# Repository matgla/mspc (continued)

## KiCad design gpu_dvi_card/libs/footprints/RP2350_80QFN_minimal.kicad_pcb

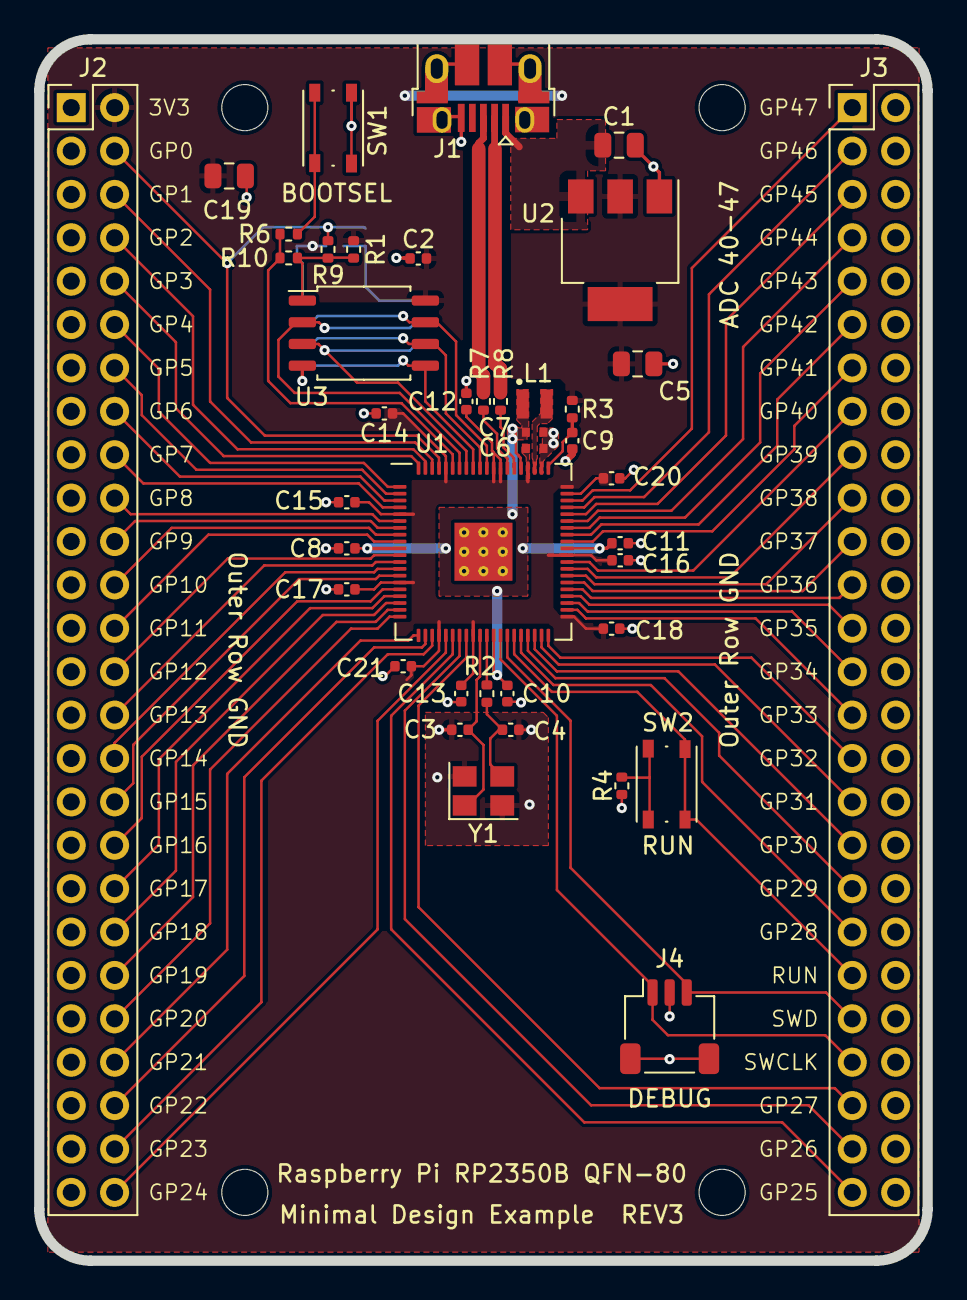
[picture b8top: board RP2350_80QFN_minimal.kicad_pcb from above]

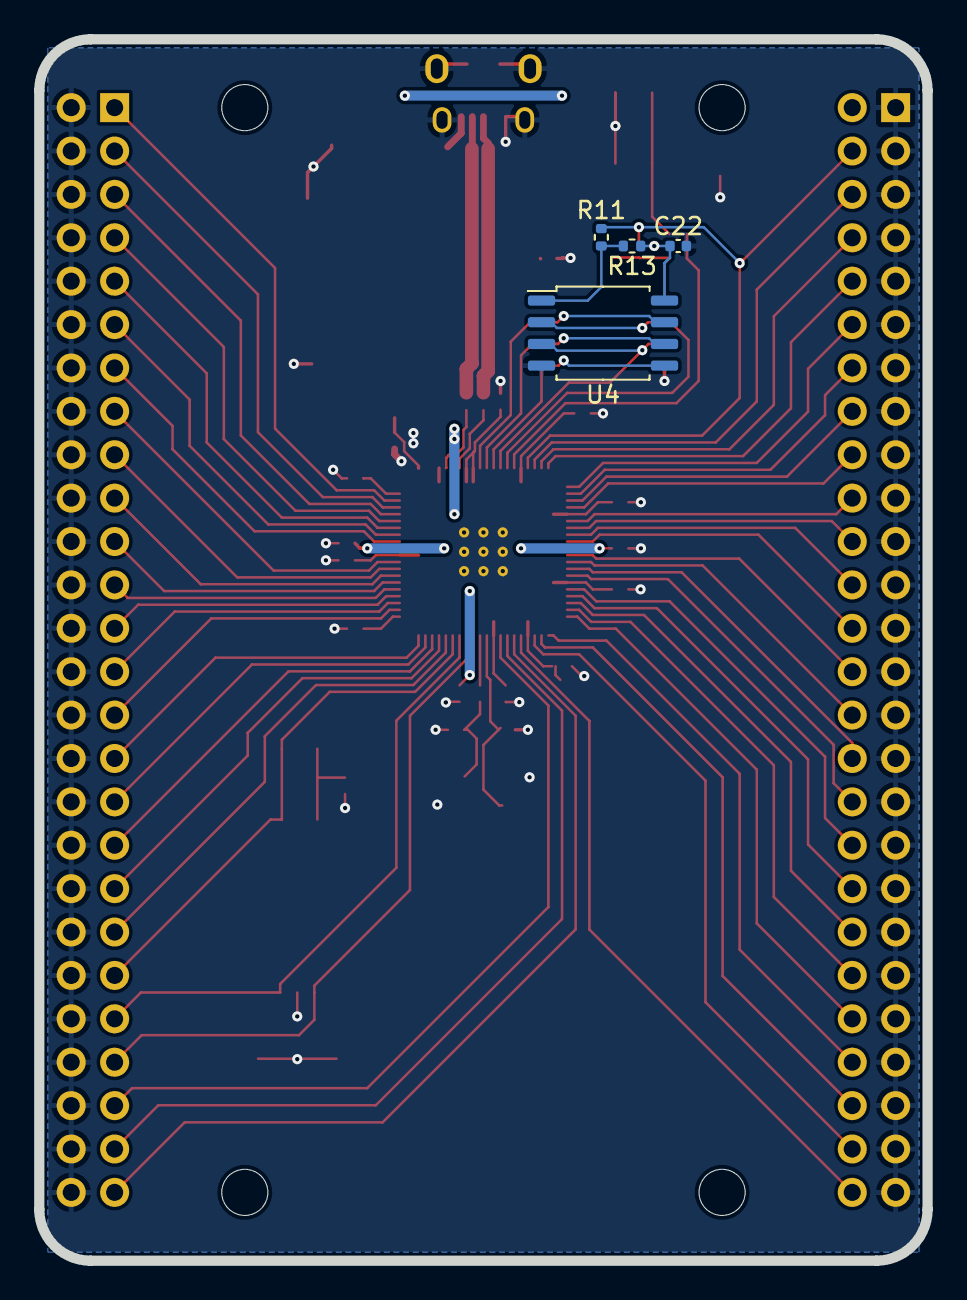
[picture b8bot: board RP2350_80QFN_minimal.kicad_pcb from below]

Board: 2 copper layers, 52.0 x 71.5 mm, 49 parts (4 on the bottom side), 74 nets.

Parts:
C1, C5, C19: 10u; C_0805_2012Metric
C2, C8, C11, C12, C13, C14, C15, C16, C17, C18, C20, C21: 100n; C_0402_1005Metric
C3, C4: 15p; C_0402_1005Metric
C6, C7: 4.7u; C_0402_1005Metric_small_pads
C9, C10: 4.7u; C_0402_1005Metric
C22: DNF; C_0402_1005Metric
H1, H2, H3, H4: MountingHole; MountingHole_2.7mm_M2.5
J1: USB_B_Micro; USB_Micro-B_Amphenol_10103594-0001LF_Horizontal
J2, J3: Conn_02x26_Odd_Even; PinHeader_2x26_P2.54mm_Vertical
J4: SM03B-SRSS-TB; JST_SH_SM03B-SRSS-TB_1x03-1MP_P1.00mm_Horizontal
L1: 3.3u; L_pol_2016
R1, R9, R11, R13: DNF; R_0402_1005Metric
R2, R4, R6: 1k; R_0402_1005Metric
R3: 33; R_0402_1005Metric
R7, R8: 27; R_0402_1005Metric
R10: 0; R_0402_1005Metric
SW1, SW2: SW_Push; SW_Push_1P1T_NO_Vertical_Wuerth_434133025816
U1: RP2350_80QFN; RP2350-QFN-80-1EP_10x10_P0.4mm_EP3.4x3.4mm_ThermalVias
U2: NCP1117-3.3_SOT223; SOT-223-3_TabPin2
U3: W25Q128JVS; SOIC-8_5.23x5.23mm_P1.27mm
U4: DNF; SOIC-8_5.23x5.23mm_P1.27mm
Y1: ABM8-272-T3; Crystal_SMD_3225-4Pin_3.2x2.5mm

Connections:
+1V1: C7.1, C8.1, C10.1, C11.1, L1.1, U1.10 (DVDD), U1.32 (DVDD), U1.51 (DVDD), U1.65 (VREG_FB)
+3V3: C2.1, C5.1, C6.1, C12.1, C13.1, C14.1, C15.1, C16.1, C17.1, C18.1, C19.1, C20.1, C21.1, C22.1, J2.2, R1.1, R3.1, R13.1, U1.5 (IOVDD), U1.15 (IOVDD), U1.24 (IOVDD), U1.29 (IOVDD), U1.41 (IOVDD), U1.50 (IOVDD), U1.59 (ADC_AVDD), U1.60 (IOVDD), U1.64 (VREG_VIN), U1.68 (USB_OTP_VDD), U1.69 (QSPI_IOVDD), U1.76 (IOVDD), U2.2 (VO), U3.8 (VCC), U4.8 (VCC)
/FLASH2_SS: R11.2, R13.2, U4.1 (~CS)
/FLASH_SS: R1.2, R9.2, R10.2, U3.1 (~CS)
/GPIO0: J2.4, R9.1, R11.1, U1.77 (GPIO0)
/GPIO1: J2.6, U1.78 (GPIO1)
/GPIO2: J2.8, U1.79 (GPIO2)
/GPIO3: J2.10, U1.80 (GPIO3)
/GPIO4: J2.12, U1.1 (GPIO4)
/GPIO5: J2.14, U1.2 (GPIO5)
/GPIO6: J2.16, U1.3 (GPIO6)
/GPIO7: J2.18, U1.4 (GPIO7)
/GPIO8: J2.20, U1.6 (GPIO8)
/GPIO9: J2.22, U1.7 (GPIO9)
/GPIO10: J2.24, U1.8 (GPIO10)
/GPIO11: J2.26, U1.9 (GPIO11)
/GPIO12: J2.28, U1.11 (GPIO12)
/GPIO13: J2.30, U1.12 (GPIO13)
/GPIO14: J2.32, U1.13 (GPIO14)
/GPIO15: J2.34, U1.14 (GPIO15)
/GPIO16: J2.36, U1.16 (GPIO16)
/GPIO17: J2.38, U1.17 (GPIO17)
/GPIO18: J2.40, U1.18 (GPIO18)
/GPIO19: J2.42, U1.19 (GPIO19)
/GPIO20: J2.44, U1.20 (GPIO20)
/GPIO21: J2.46, U1.21 (GPIO21)
/GPIO22: J2.48, U1.22 (GPIO22)
/GPIO23: J2.50, U1.23 (GPIO23)
/GPIO24: J2.52, U1.25 (GPIO24)
/GPIO25: J3.51, U1.26 (GPIO25)
/GPIO26: J3.49, U1.27 (GPIO26)
/GPIO27: J3.47, U1.28 (GPIO27)
/GPIO28: J3.39, U1.36 (GPIO28)
/GPIO29: J3.37, U1.37 (GPIO29)
/GPIO30: J3.35, U1.38 (GPIO30)
/GPIO31: J3.33, U1.39 (GPIO31)
/GPIO32: J3.31, U1.40 (GPIO32)
/GPIO33: J3.29, U1.42 (GPIO33)
/GPIO34: J3.27, U1.43 (GPIO34)
/GPIO35: J3.25, U1.44 (GPIO35)
/GPIO36: J3.23, U1.45 (GPIO36)
/GPIO37: J3.21, U1.46 (GPIO37)
/GPIO38: J3.19, U1.47 (GPIO38)
/GPIO39: J3.17, U1.48 (GPIO39)
/GPIO40_ADC0: J3.15, U1.49 (GPIO40_ADC0)
/GPIO41_ADC1: J3.13, U1.52 (GPIO41_ADC1)
/GPIO42_ADC2: J3.11, U1.53 (GPIO42_ADC2)
/GPIO43_ADC3: J3.9, U1.54 (GPIO43_ADC3)
/GPIO44_ADC4: J3.7, U1.55 (GPIO44_ADC4)
/GPIO45_ADC5: J3.5, U1.56 (GPIO45_ADC5)
/GPIO46_ADC6: J3.3, U1.57 (GPIO46_ADC6)
/GPIO47_ADC7: J3.1, U1.58 (GPIO47_ADC7)
/QSPI_SCLK: U1.71 (QSPI_SCLK), U3.6 (CLK), U4.6 (CLK)
/QSPI_SD0: U1.72 (QSPI_SD0), U3.5 (DI(IO0)), U4.5 (DI(IO0))
/QSPI_SD1: U1.74 (QSPI_SD1), U3.2 (DO(IO1)), U4.2 (DO(IO1))
/QSPI_SD2: U1.73 (QSPI_SD2), U3.3 (IO2), U4.3 (IO2)
/QSPI_SD3: U1.70 (QSPI_SD3), U3.7 (IO3), U4.7 (IO3)
/QSPI_SS: R6.1, R10.1, U1.75 (QSPI_SS)
/RUN: J3.41, SW2.2, U1.35 (RUN)
/SWCLK: J3.45, J4.1, U1.33 (SWCLK)
/SWD: J3.43, J4.3, U1.34 (SWD)
/USB_D+: J1.3 (D+), R7.1
/USB_D-: J1.2 (D-), R8.1
/VREG_AVDD: C9.1, R3.2, U1.61 (VREG_AVDD)
/VREG_LX: L1.2, U1.63 (VREG_LX)
/XIN: C3.1, U1.30 (XIN), Y1.1
/XOUT: R2.1, U1.31 (XOUT)
/~USB_BOOT: R6.2, SW1.2
GND: C1.2, C2.2, C3.2, C4.2, C5.2, C6.2, C7.2, C8.2, C9.2, C10.2, C11.2, C12.2, C13.2, C14.2, C15.2, C16.2, C17.2, C18.2, C19.2, C20.2, C21.2, C22.2, J1.5 (GND), J1.6 (Shield), J2.1, J2.3, J2.5, J2.7, J2.9, J2.11, J2.13, J2.15, J2.17, J2.19, J2.21, J2.23, J2.25, J2.27, J2.29, J2.31, J2.33, J2.35, J2.37, J2.39, J2.41, J2.43, J2.45, J2.47, J2.49, J2.51, J3.2, J3.4, J3.6, J3.8, J3.10, J3.12, J3.14, J3.16, J3.18, J3.20, J3.22, J3.24, J3.26, J3.28, J3.30, J3.32, J3.34, J3.36, J3.38, J3.40, J3.42, J3.44, J3.46, J3.48, J3.50, J3.52, J4.2, J4.MP (MountPin), R4.2, SW1.1, U1.62 (VREG_PGND), U1.81 (GND), U2.1 (GND), U3.4 (GND), U4.4 (GND), Y1.2, Y1.4
unnamed: C4.1, R2.2, Y1.3
unnamed: R4.1, SW2.1
unnamed: R8.2, U1.66 (USB_DM)
unnamed: R7.2, U1.67 (USB_DP)
VBUS: C1.1, J1.1 (VBUS), U2.3 (VI)

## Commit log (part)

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2022-02-11 decoupling capacitors placed
2022-02-20 working on new version of fpga extension with Lattice FPGA
2022-02-21 qspi added
2022-04-10 motherboard almost done, power section must be added
2022-04-15 Fixing labels
2022-04-16 fixed warnings and errors
2022-04-29 board almost ready, paths must be aligned
2022-04-30 motherboard designed
2022-07-04 some changes
2022-11-10 schematic for gpu extension
2022-11-10 some ERC fixes
2022-11-13 some fixes for ERC
2022-11-16 gpu and motherboard passes tests, now time for fpga
2022-11-29 refactored mainboard schematic
2022-12-06 working on new pcb
2022-12-09 working on PCB
2022-12-11 Mainboard rev 1.0a prepared
2022-12-11 fixes in gpu extension schematic
2022-12-21 fixes
2023-01-19 version 1.0
2023-01-20 new gpu stencil
2023-01-20 new mainboard stencil
2024-08-25 prepared first versions of PCBs
2024-08-25 added outputs and gerbers
2024-11-28 fixed trace to flash memory
2024-12-19 vga and dvi cards separated
